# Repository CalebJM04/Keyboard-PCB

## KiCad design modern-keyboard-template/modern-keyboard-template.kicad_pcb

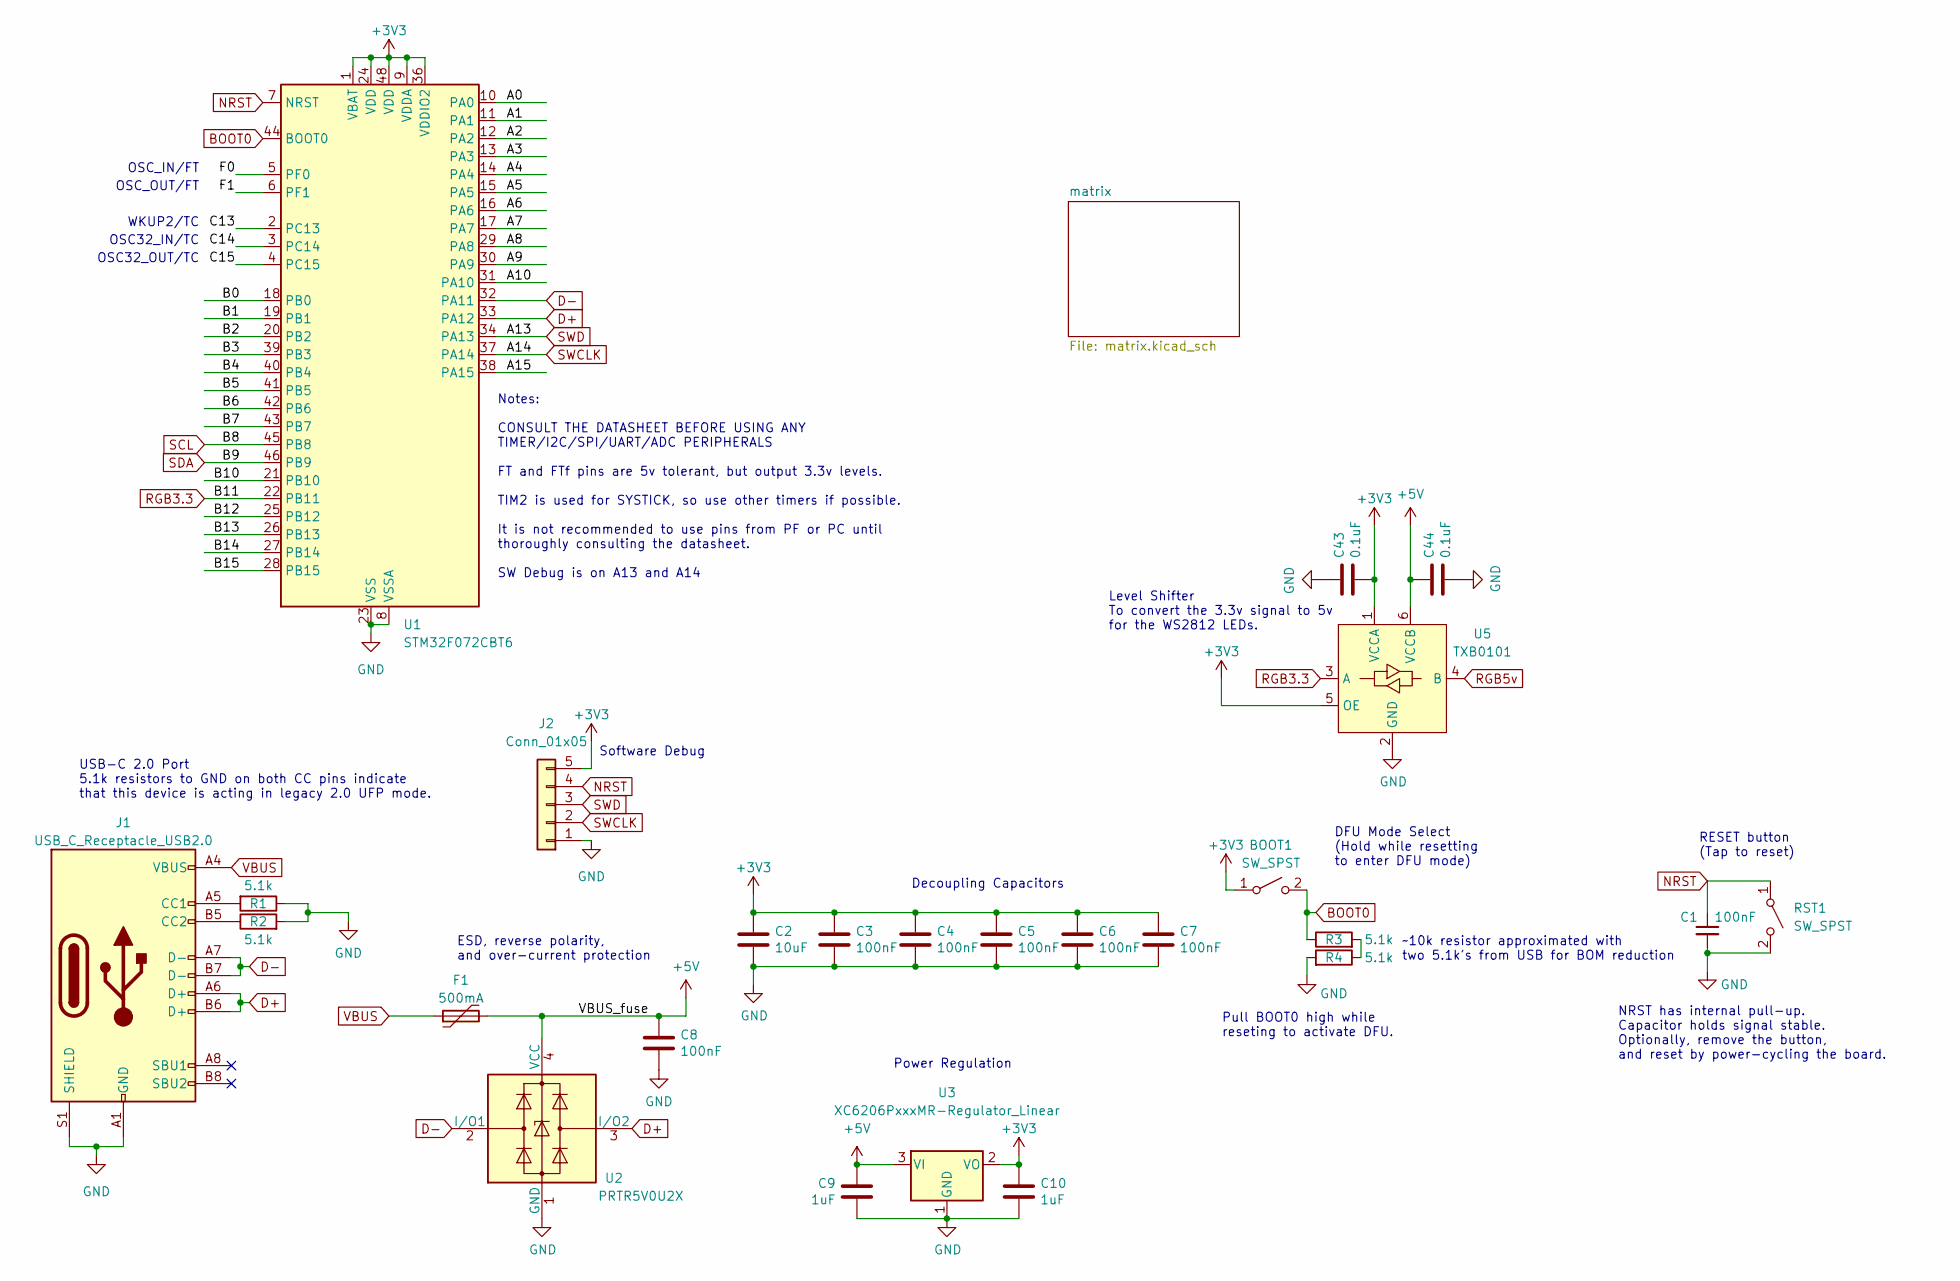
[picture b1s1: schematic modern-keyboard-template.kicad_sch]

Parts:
BOOT1: SW_SPST; SW_SPST_TL3342
C1, C3, C4, C5, C6, C7, C8: 100nF; C_0402_1005Metric; LCSC C307331
C2: 10uF; C_0603_1608Metric; LCSC C307331
C9, C10: 1uF; C_0402_1005Metric; LCSC C307331
C43, C44: 0.1uF; C_0402_1005Metric; LCSC C307331
F1: 500mA; Fuse_1206_3216Metric; LCSC C135341
J1: USB_C_Receptacle_USB2.0; USB_C_Receptacle_HRO_TYPE-C-31-M-12; JlcRotOffset 180
J2: Conn_01x05; PinHeader_1x05_P2.54mm_Vertical
R1, R2, R3, R4: 5.1k; R_0402_1005Metric
RST1: SW_SPST; SW_SPST_TL3342
U1: STM32F072CBT6; LQFP-48_7x7mm_P0.5mm; JlcRotOffset 90
U2: PRTR5V0U2X; SOT-143; LCSC C2827688
U3: XC6206PxxxMR-Regulator_Linear; SOT-23; LCSC C5446
U5: TXB0101; SOT-363_SC-70-6_Handsoldering; LCSC C324081

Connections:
+3V3: BOOT1.1 (A), C2.1, C3.1, C4.1, C5.1, C6.1, C7.1, C10.1, C43.2, J2.5, U1.1 (VBAT), U1.9 (VDDA), U1.24 (VDD), U1.36 (VDDIO2), U1.48 (VDD), U3.2 (VO), U5.1 (VCCA), U5.5 (OE)
+5V: C8.1, C9.1, C44.1, F1.2, U2.4 (VCC), U3.3 (VI), U5.6 (VCCB)
/A0: U1.10 (PA0)
/A1: U1.11 (PA1)
/A2: U1.12 (PA2)
/A3: U1.13 (PA3)
/A4: U1.14 (PA4)
/A5: U1.15 (PA5)
/A6: U1.16 (PA6)
/A7: U1.17 (PA7)
/A8: U1.29 (PA8)
/A9: U1.30 (PA9)
/A10: U1.31 (PA10)
/A15: U1.38 (PA15)
/B0: U1.18 (PB0)
/B1: U1.19 (PB1)
/B2: U1.20 (PB2)
/B3: U1.39 (PB3)
/B4: U1.40 (PB4)
/B5: U1.41 (PB5)
/B6: U1.42 (PB6)
/B7: U1.43 (PB7)
/B10: U1.21 (PB10)
/B12: U1.25 (PB12)
/B13: U1.26 (PB13)
/B14: U1.27 (PB14)
/B15: U1.28 (PB15)
/C13: U1.2 (PC13)
/C14: U1.3 (PC14)
/C15: U1.4 (PC15)
/F0: U1.5 (PF0)
/F1: U1.6 (PF1)
BOOT0: BOOT1.2 (B), R3.1, U1.44 (BOOT0)
D+: J1.A6 (D+), J1.B6 (D+), U1.33 (PA12), U2.3 (I/O2)
D-: J1.A7 (D-), J1.B7 (D-), U1.32 (PA11), U2.2 (I/O1)
GND: C1.2, C2.2, C3.2, C4.2, C5.2, C6.2, C7.2, C8.2, C9.2, C10.2, C43.1, C44.2, J1.A1 (GND), J1.A12 (GND), J1.B1 (GND), J1.B12 (GND), J1.S1 (SHIELD), J2.1, R1.1, R2.2, R4.2, RST1.2 (B), U1.8 (VSSA), U1.23 (VSS), U1.35 (VSS), U1.47 (VSS), U2.1 (GND), U3.1 (GND), U5.2 (GND)
NRST: C1.1, J2.4, RST1.1 (A), U1.7 (NRST)
unnamed: J1.A5 (CC1), R1.2
unnamed: J1.B5 (CC2), R2.1
unnamed: R3.2, R4.1
RGB3.3: U1.22 (PB11), U5.3 (A)
RGB5v: U5.4 (B)
SCL: U1.45 (PB8)
SDA: U1.46 (PB9)
SWCLK: J2.2, U1.37 (PA14)
SWD: J2.3, U1.34 (PA13)
VBUS: F1.1, J1.A4 (VBUS), J1.A9 (VBUS), J1.B4 (VBUS), J1.B9 (VBUS)

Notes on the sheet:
Decoupling Capacitors
~10k resistor approximated with two 5.1k's from USB for BOM reduction
Notes: CONSULT THE DATASHEET BEFORE USING ANY TIMER/I2C/SPI/UART/ADC PERIPHERALS FT and FTf pins are 5v tolerant, but output 3.3v levels. TIM2 is used for SYSTICK, so use other timers if possible. It is not recommended to use pins from PF or PC until thoroughly consulting the datasheet. SW Debug is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
RESET button (Tap to reset)
Power Regulation
OSC_IN/FT
OSC32_OUT/TC
USB-C 2.0 Port 5.1k resistors to GND on both CC pins indicate that this device is acting in legacy 2.0 UFP mode.
WKUP2/TC
OSC_OUT/FT
ESD, reverse polarity, and over-current protection
Software Debug
NRST has internal pull-up. Capacitor holds signal stable. Optionally, remove the button, and reset by power-cycling the board.
OSC32_IN/TC
Pull BOOT0 high while reseting to activate DFU.
Level Shifter To convert the 3.3v signal to 5v for the WS2812 LEDs.
DFU Mode Select (Hold while resetting to enter DFU mode)

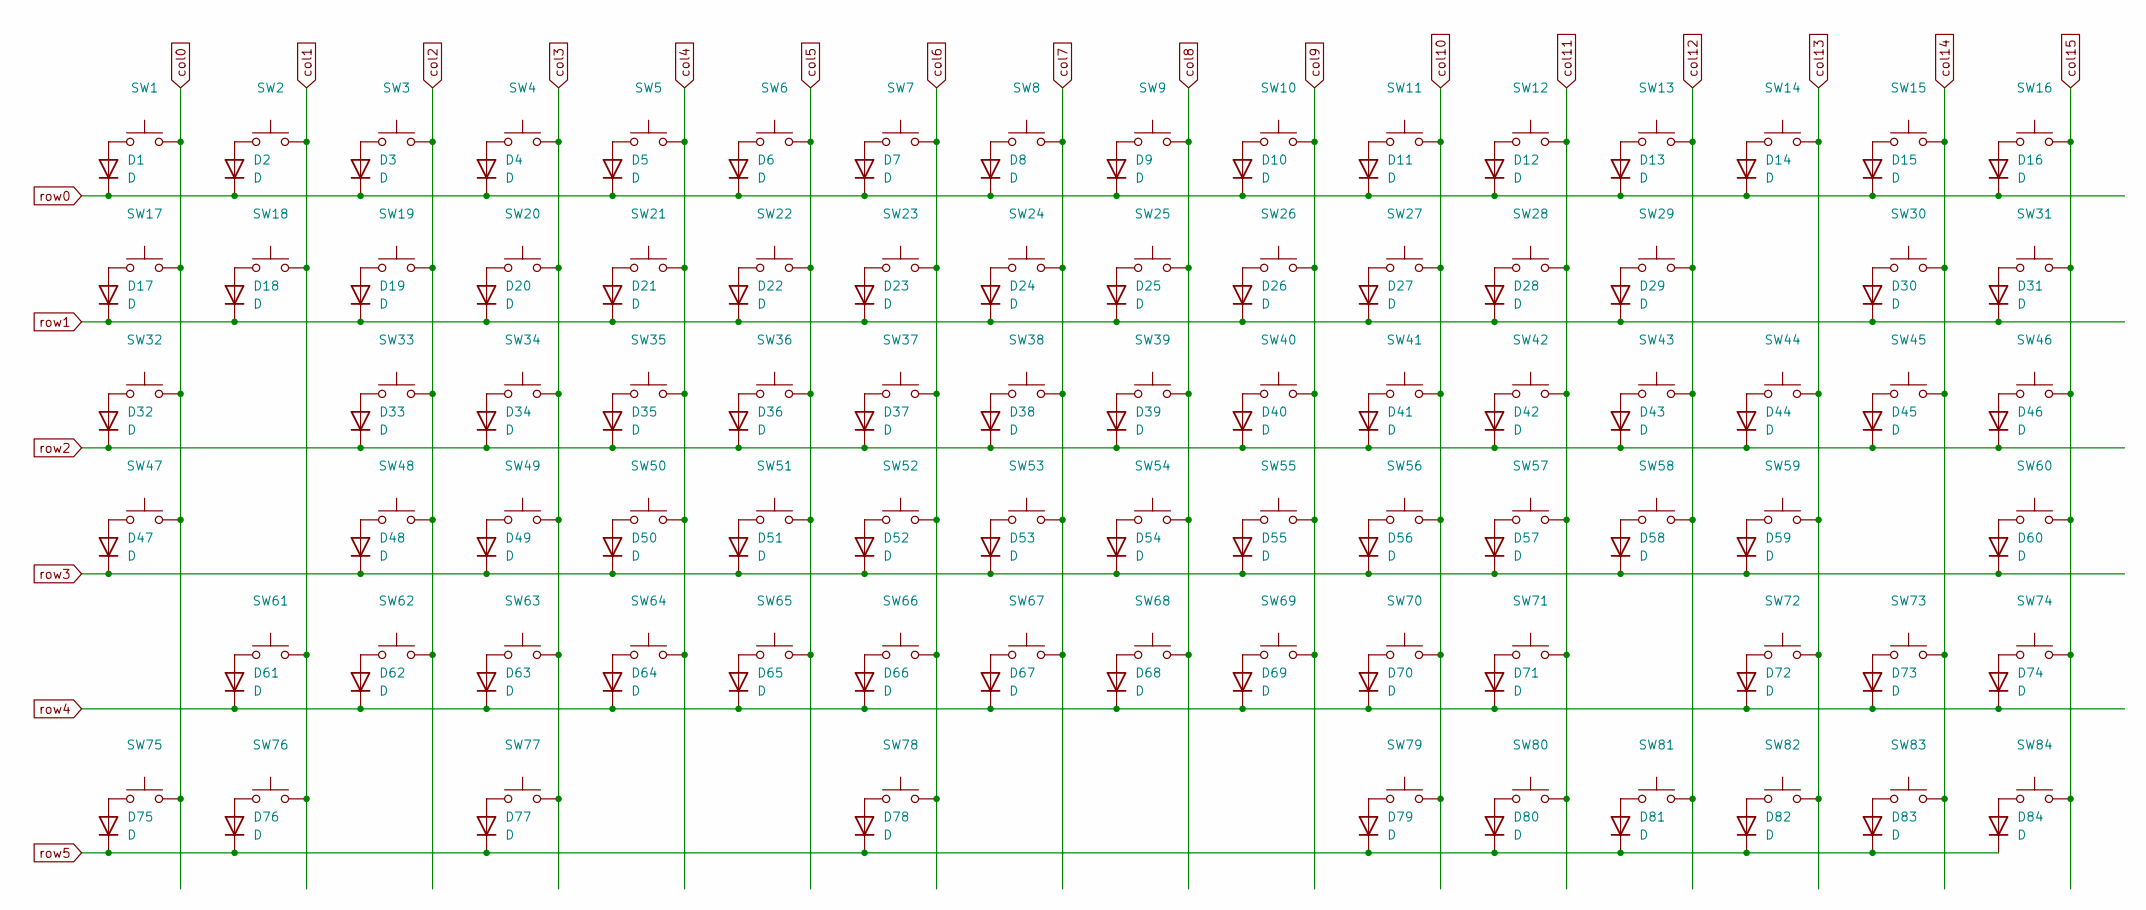
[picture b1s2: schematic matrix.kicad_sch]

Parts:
D1, D2, D3, D4, D5, D6, D7, D8, D9, D10, D11, D12, D13, D14, D15, D16, D17, D18, D19, D20, D21, D22, D23, D24, D25, D26, D27, D28, D29, D30, D31, D32, D33, D34, D35, D36, D37, D38, D39, D40, D41, D42, D43, D44, D45, D46, D47, D48, D49, D50, D51, D52, D53, D54, D55, D56, D57, D58, D59, D60, D61, D62, D63, D64, D65, D66, D67, D68, D69, D70, D71, D72, D73, D74, D75, D76, D77, D78, D79, D80, D81, D82, D83, D84: D; D_SOD-123
SW1, SW2, SW3, SW4, SW5, SW6, SW7, SW8, SW9, SW10, SW11, SW12, SW13, SW14, SW15, SW16, SW17, SW18, SW19, SW20, SW21, SW22, SW23, SW24, SW25, SW26, SW27, SW28, SW29, SW30, SW31, SW32, SW33, SW34, SW35, SW36, SW37, SW38, SW39, SW40, SW41, SW42, SW43, SW44, SW45, SW46, SW47, SW48, SW49, SW50, SW51, SW52, SW53, SW54, SW55, SW56, SW57, SW58, SW59, SW60, SW61, SW62, SW63, SW64, SW65, SW66, SW67, SW68, SW69, SW70, SW71, SW72, SW73, SW74, SW75, SW76, SW77, SW78, SW79, SW80, SW81, SW82, SW83, SW84: Kailh_socket_MX

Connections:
unnamed: D1.2 (A), SW1.1
unnamed: D2.2 (A), SW2.1
unnamed: D3.2 (A), SW3.1
unnamed: D4.2 (A), SW4.1
unnamed: D5.2 (A), SW5.1
unnamed: D6.2 (A), SW6.1
unnamed: D7.2 (A), SW7.1
unnamed: D8.2 (A), SW8.1
unnamed: D9.2 (A), SW9.1
unnamed: D10.2 (A), SW10.1
unnamed: D11.2 (A), SW11.1
unnamed: D12.2 (A), SW12.1
unnamed: D13.2 (A), SW13.1
unnamed: D14.2 (A), SW14.1
unnamed: D15.2 (A), SW15.1
unnamed: D16.2 (A), SW16.1
unnamed: D17.2 (A), SW17.1
unnamed: D18.2 (A), SW18.1
unnamed: D19.2 (A), SW19.1
unnamed: D20.2 (A), SW20.1
unnamed: D21.2 (A), SW21.1
unnamed: D22.2 (A), SW22.1
unnamed: D23.2 (A), SW23.1
unnamed: D24.2 (A), SW24.1
unnamed: D25.2 (A), SW25.1
unnamed: D26.2 (A), SW26.1
unnamed: D27.2 (A), SW27.1
unnamed: D28.2 (A), SW28.1
unnamed: D29.2 (A), SW29.1
unnamed: D30.2 (A), SW30.1
unnamed: D31.2 (A), SW31.1
unnamed: D32.2 (A), SW32.1
unnamed: D33.2 (A), SW33.1
unnamed: D34.2 (A), SW34.1
unnamed: D35.2 (A), SW35.1
unnamed: D36.2 (A), SW36.1
unnamed: D37.2 (A), SW37.1
unnamed: D38.2 (A), SW38.1
unnamed: D39.2 (A), SW39.1
unnamed: D40.2 (A), SW40.1
unnamed: D41.2 (A), SW41.1
unnamed: D42.2 (A), SW42.1
unnamed: D43.2 (A), SW43.1
unnamed: D44.2 (A), SW44.1
unnamed: D45.2 (A), SW45.1
unnamed: D46.2 (A), SW46.1
unnamed: D47.2 (A), SW47.1
unnamed: D48.2 (A), SW48.1
unnamed: D49.2 (A), SW49.1
unnamed: D50.2 (A), SW50.1
unnamed: D51.2 (A), SW51.1
unnamed: D52.2 (A), SW52.1
unnamed: D53.2 (A), SW53.1
unnamed: D54.2 (A), SW54.1
unnamed: D55.2 (A), SW55.1
unnamed: D56.2 (A), SW56.1
unnamed: D57.2 (A), SW57.1
unnamed: D58.2 (A), SW58.1
unnamed: D59.2 (A), SW59.1
unnamed: D60.2 (A), SW60.1
unnamed: D61.2 (A), SW61.1
unnamed: D62.2 (A), SW62.1
unnamed: D63.2 (A), SW63.1
unnamed: D64.2 (A), SW64.1
unnamed: D65.2 (A), SW65.1
unnamed: D66.2 (A), SW66.1
unnamed: D67.2 (A), SW67.1
unnamed: D68.2 (A), SW68.1
unnamed: D69.2 (A), SW69.1
unnamed: D70.2 (A), SW70.1
unnamed: D71.2 (A), SW71.1
unnamed: D72.2 (A), SW72.1
unnamed: D73.2 (A), SW73.1
unnamed: D74.2 (A), SW74.1
unnamed: D75.2 (A), SW75.1
unnamed: D76.2 (A), SW76.1
unnamed: D77.2 (A), SW77.1
unnamed: D78.2 (A), SW78.1
unnamed: D79.2 (A), SW79.1
unnamed: D80.2 (A), SW80.1
unnamed: D81.2 (A), SW81.1
unnamed: D82.2 (A), SW82.1
unnamed: D83.2 (A), SW83.1
unnamed: D84.2 (A), SW84.1
col0: SW1.2, SW17.2, SW32.2, SW47.2, SW75.2
col1: SW2.2, SW18.2, SW61.2, SW76.2
col2: SW3.2, SW19.2, SW33.2, SW48.2, SW62.2
col3: SW4.2, SW20.2, SW34.2, SW49.2, SW63.2, SW77.2
col4: SW5.2, SW21.2, SW35.2, SW50.2, SW64.2
col5: SW6.2, SW22.2, SW36.2, SW51.2, SW65.2
col6: SW7.2, SW23.2, SW37.2, SW52.2, SW66.2, SW78.2
col7: SW8.2, SW24.2, SW38.2, SW53.2, SW67.2
col8: SW9.2, SW25.2, SW39.2, SW54.2, SW68.2
col9: SW10.2, SW26.2, SW40.2, SW55.2, SW69.2
col10: SW11.2, SW27.2, SW41.2, SW56.2, SW70.2, SW79.2
col11: SW12.2, SW28.2, SW42.2, SW57.2, SW71.2, SW80.2
col12: SW13.2, SW29.2, SW43.2, SW58.2, SW81.2
col13: SW14.2, SW44.2, SW59.2, SW72.2, SW82.2
col14: SW15.2, SW30.2, SW45.2, SW73.2, SW83.2
col15: SW16.2, SW31.2, SW46.2, SW60.2, SW74.2, SW84.2
row0: D1.1 (K), D2.1 (K), D3.1 (K), D4.1 (K), D5.1 (K), D6.1 (K), D7.1 (K), D8.1 (K), D9.1 (K), D10.1 (K), D11.1 (K), D12.1 (K), D13.1 (K), D14.1 (K), D15.1 (K), D16.1 (K)
row1: D17.1 (K), D18.1 (K), D19.1 (K), D20.1 (K), D21.1 (K), D22.1 (K), D23.1 (K), D24.1 (K), D25.1 (K), D26.1 (K), D27.1 (K), D28.1 (K), D29.1 (K), D30.1 (K), D31.1 (K)
row2: D32.1 (K), D33.1 (K), D34.1 (K), D35.1 (K), D36.1 (K), D37.1 (K), D38.1 (K), D39.1 (K), D40.1 (K), D41.1 (K), D42.1 (K), D43.1 (K), D44.1 (K), D45.1 (K), D46.1 (K)
row3: D47.1 (K), D48.1 (K), D49.1 (K), D50.1 (K), D51.1 (K), D52.1 (K), D53.1 (K), D54.1 (K), D55.1 (K), D56.1 (K), D57.1 (K), D58.1 (K), D59.1 (K), D60.1 (K)
row4: D61.1 (K), D62.1 (K), D63.1 (K), D64.1 (K), D65.1 (K), D66.1 (K), D67.1 (K), D68.1 (K), D69.1 (K), D70.1 (K), D71.1 (K), D72.1 (K), D73.1 (K), D74.1 (K)
row5: D75.1 (K), D76.1 (K), D77.1 (K), D78.1 (K), D79.1 (K), D80.1 (K), D81.1 (K), D82.1 (K), D83.1 (K), D84.1 (K)

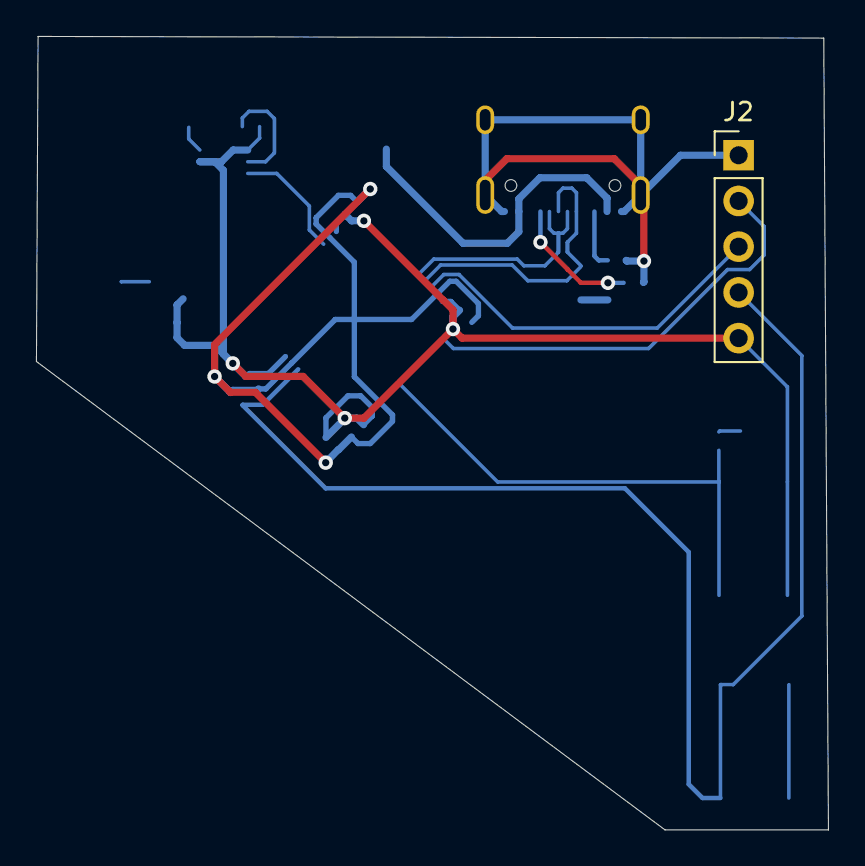
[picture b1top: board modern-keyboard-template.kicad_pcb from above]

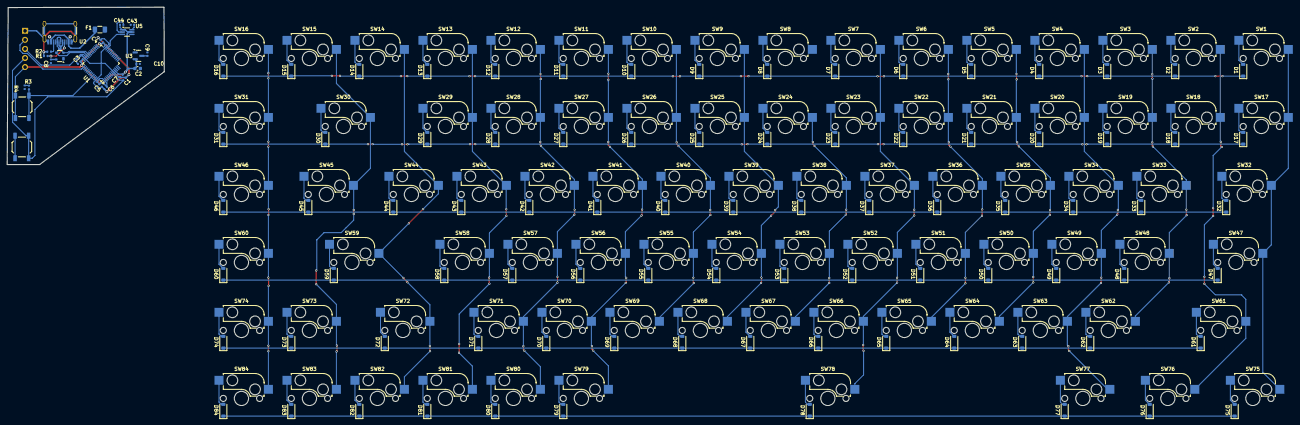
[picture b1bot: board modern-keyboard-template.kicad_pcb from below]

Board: 2 copper layers, 193 parts (108 on the bottom side), 120 nets.

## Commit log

2025-09-02 initial commit of keyboard
2025-09-02 created matrix sheet
2025-09-02 updated matrix and added dependencies
2025-09-03 updated pcb w/ switches
    need to revisit this entire design tbh
2025-09-11 added layout file, router keys
    added layout file in /dependencies
2025-11-11 updated usb position so edge is at edge of board
    i ordered it without this oh please please pleaseeee fit 🙏
